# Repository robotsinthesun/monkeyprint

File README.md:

# monkeyprint
A simple tool for pre-processing 3d models and controlling 3d DLP printers.

## What is *monkeyprint* for?
*monkeyprint* came into existence as an open source, will-natively-run-on-linux alternative to [*Creation Workshop*](http://www.envisionlabs.net/home.html).

Thanks to the latest efforts it also runs on Windows although it has not been thoroughly tested yet...

####*monkeyprint* allows you to:

* load one or multiple stl files
* define the position, scale or rotation in the printers build volume
* generate supports with some simple parameters
* hollow the model and create fill structures
* slice the model with a specific layer height
* control a print job on your DLP printer via serial port using G-Code commands

In order for *monkeyprint* to work you need a 3d DLP printer that can receive G-Code commands via serial port and has a projector that is connected to your PC.

## Installation

#### Dependencies
*monkeyprint* is programmed in Python 2.7 and uses the following libraries:

* `PyQt4` for the GUI
* `VTK` for stl processing and slicing
* `openCV` for slice image handling
* `numpy` for slice image handling
* `pyserial` and `zmq` for communication

#### Linux installation

\* **Using a virtualenv**

Create a virtual env with python2.7 as the interpreter and activate it.

For installing PyQt4, execute the following commands (assigning your virtualenv 
path to the $virtual_env_path variable)

```bash
$  sudo apt-get install python-qt4

$  $virtual_env_path="your/virtualenv/path"
$  cp -R  /usr/lib/python2.7/dist-packages/sip* $virtual_env_path/lib/python2.7/site-packages
$  mkdir $virtual_env_path/lib/python2.7/site-packages/PyQt4/
$  cp -R  /usr/lib/python2.7/dist-packages/PyQt4/* $virtual_env_path/lib/python2.7/site-packages/PyQt4/

```

```bash
$  pip install -r /monkeyprint_repo_path/requirements.txt
```

\* **Installing globally**

First, install the dependencies.
On Debian-based distros like Ubuntu, you can install the relevant packages using the following command:

`sudo apt-get install git-core python-qt4 libvtk5.8 libopencv-core2.4 python2.7 python-vtk python-numpy python-opencv python-imaging python-serial python-zmq`

Once the dependencies are installed, simply download *monkeyprint* using git:

`git clone git://github.com/robotsinthesun/monkeyprint.git`

This will create a monkeyprint folder in your current location. You can then start *monkeyprint* by running `python monkeyprint.py` from within that folder.

#### Windows installation

Windows users simply download the latest release [here](https://github.com/robotsinthesun/monkeyprint/releases). It's an exe that contains Python and all the necessary libraries. No need to install anything. Yep.

#### Hardware
*monkeyprint* controls your printer using G-Code, so if your printer connects via serial or usb and understands G-Code, you're good to go. Alternatively, you can define custom string commands if your board uses some other language.

## Basic setup

Before starting to use *monkeyprint* with your printer, it is necessary to adjust some of the settings to fit your machine.

Start *monkeyprint*, click *Options* in the top menu and select *Settings*. A dialog will come up.

#### Main settings
In the first tab, make sure to correctly set

* your printers build volume (the size of the area illuminated by your projector and the draw of your Z-axis),
* the serial connection to your printer's controller board. On Linux, this will most likely be `/dev/ttyACM0` or `/dev/ttyUSB0` if you're connecting via USB or `/dev/ttyS0` if using an old-school Sub-D serial connection while on Windows it will be something like `COM0` or `COM1`. The baud rate depends on the board you use and should be in the manual. On most boards it will be `57600` or `115200`.

Adjust the *Max. preview slices* if you wish. In the slicer preview, you will be presented an evently spaced number of preview slices as a subsample of all the slices. The default of 300 should be enough as the slider does not allow for finer control anyways.

Tick the *Multi body slicing* option if your model contains intersecting objects within the same stl file.

#### Projector settings
In the second tab the projector settings will be set up. These are

* your projectors resolution in pixels. This should be self-explaining...
* your projectors "position", i.e. the location of it's top left corner in relation to the whole desktop. For *monkeyprint* to work, your projector should be connected via *HDMI* and should be set to *extend* the desktop. So, if you move your mouse beyond one of the sides of your main screen, it should appear on the projector. If the projector is to the right of your main screen and the latter has a resolution of 1024 x 768 pixels, your projectors position will most likely be `1024, 0`
* an optional serial connection to your projector. Some projectors support the old Sub-D serial connector. If you get yourself a USB-to-serial adapter you will be able to connect that to your PC and power your projector on and off automatically before and after prints. The usual parameters for this connection are set as defaults, simply adjust the serial port setting to the one of your USB-to-serial adapter and it should work.

#### Print process settings
Here, you are able to construct your print process from individual modules. There are two basic types of module: internal modules and G-Code modules. While the internal modules run a distinct function like doing the exposure or simply waiting for a user-defined interval, G-Code modules send a command to your printer via serial connection.

There are three sections during a print process:

* The start section can be used to do all the tasks that bring your printer into its ready-to-print state e.g. powering up the projector, homing the build platform etc.
* The print loop section runs the commands necessary to print a slice, e.g. exposing, moving the build platform, tilting etc. for each of the slices.
* The stop section can be used to do stuff after the print has finished, e.g. moving the build platform into top position, shutting down the projector etc.

The controls below the print process list allow for adding new modules, moving the selected module up or down and deleting a selected module (except for the *Start loop* and *End loop* modules).

* To add a new module, select one from the dropdown and click the *Add* button. The new module will be inserted below the currently selected one.
* The other buttons are pretty much self-explaining I guess...
* To change the name or value of a module, simply double click the name or value in the list and enter a new one. Note: there is no checking for valid G-Code commands, so make sure they make sense and are accepted by your printer.

Here is a list of the available modules:

* *Expose*: exposes the VAT for the exposure time set in the main gui.
* *Wait*: waits for the given interval
* *Projector on / off*: Starts / shuts down your projector using the commands and serial connection specified in the *Projector settings*
* *Start / end loop*: use this to separate start, print loop and stop section
* *Custom G-Code*: sends the given command string to your printer via the serial connection specified in the main settings

## Usage

The *monkeyprint* gui is made to walk you through the pre-processing steps up to starting the print.
The model and it's position is shown in the 3d view on the left while the tabs on the right will guide you through the necessary settings.

First, load a model file by clicking the "Load model" button. Set it's scaling, position and rotation.
The model will automatically fitted to the build volume if the scaling is too large.

Proceed to the "Slicing" tab. Here you can set the overhang angle and define the geometry of the support pillars. You can also define the thickness of the bottom plate.
You can also play with the "Maximum support height" option to eliminate unwanted supports.

In the "Slicing" tab you can set the layer height and walk through the model by using the slider.
The "Print hollow" and "Use fill structures" should be self explaining. Printing hollow reduces the force on the coating of the VAT and helps to elongate the coatings life.

The "Print" tab finally let's you start the print.
Set the exposure values and hit "Print!". Complete the safety check list and there you go: your print is running!
Cancel the print by pressing "Stop". It won't stop immediately but complete the current slice and run the Stop sequence commands.

Note that you can't close the program while a print is running.

## Testing an debugging

You can simulate a serial port in order to debug the program locally:

```bash
$  socat -d -d pty,raw,echo=0 pty,raw,echo=0
```

You will receive an output like this

```bash
2019/07/30 13:01:23 socat[14810] N PTY is /dev/pts/4
2019/07/30 13:01:23 socat[14810] N PTY is /dev/pts/5
2019/07/30 13:01:23 socat[14810] N starting data transfer loop with FDs [5,5] and [7,7]
```

Now, in a new terminal execute:

```bash
$  cat < /dev/pts/4
```

*Note: The number can be different for you

Finally, inside the program settings, choose */dev/pts/5* as the serial port. Then,
start the printing.

The G-codes sent via serial port can now be monitored in the terminal.

The program will retry a command if there is no printer response. 
You can simulate the printer response by doing:

```bash
$  echo "ok" > /dev/pts/4
```

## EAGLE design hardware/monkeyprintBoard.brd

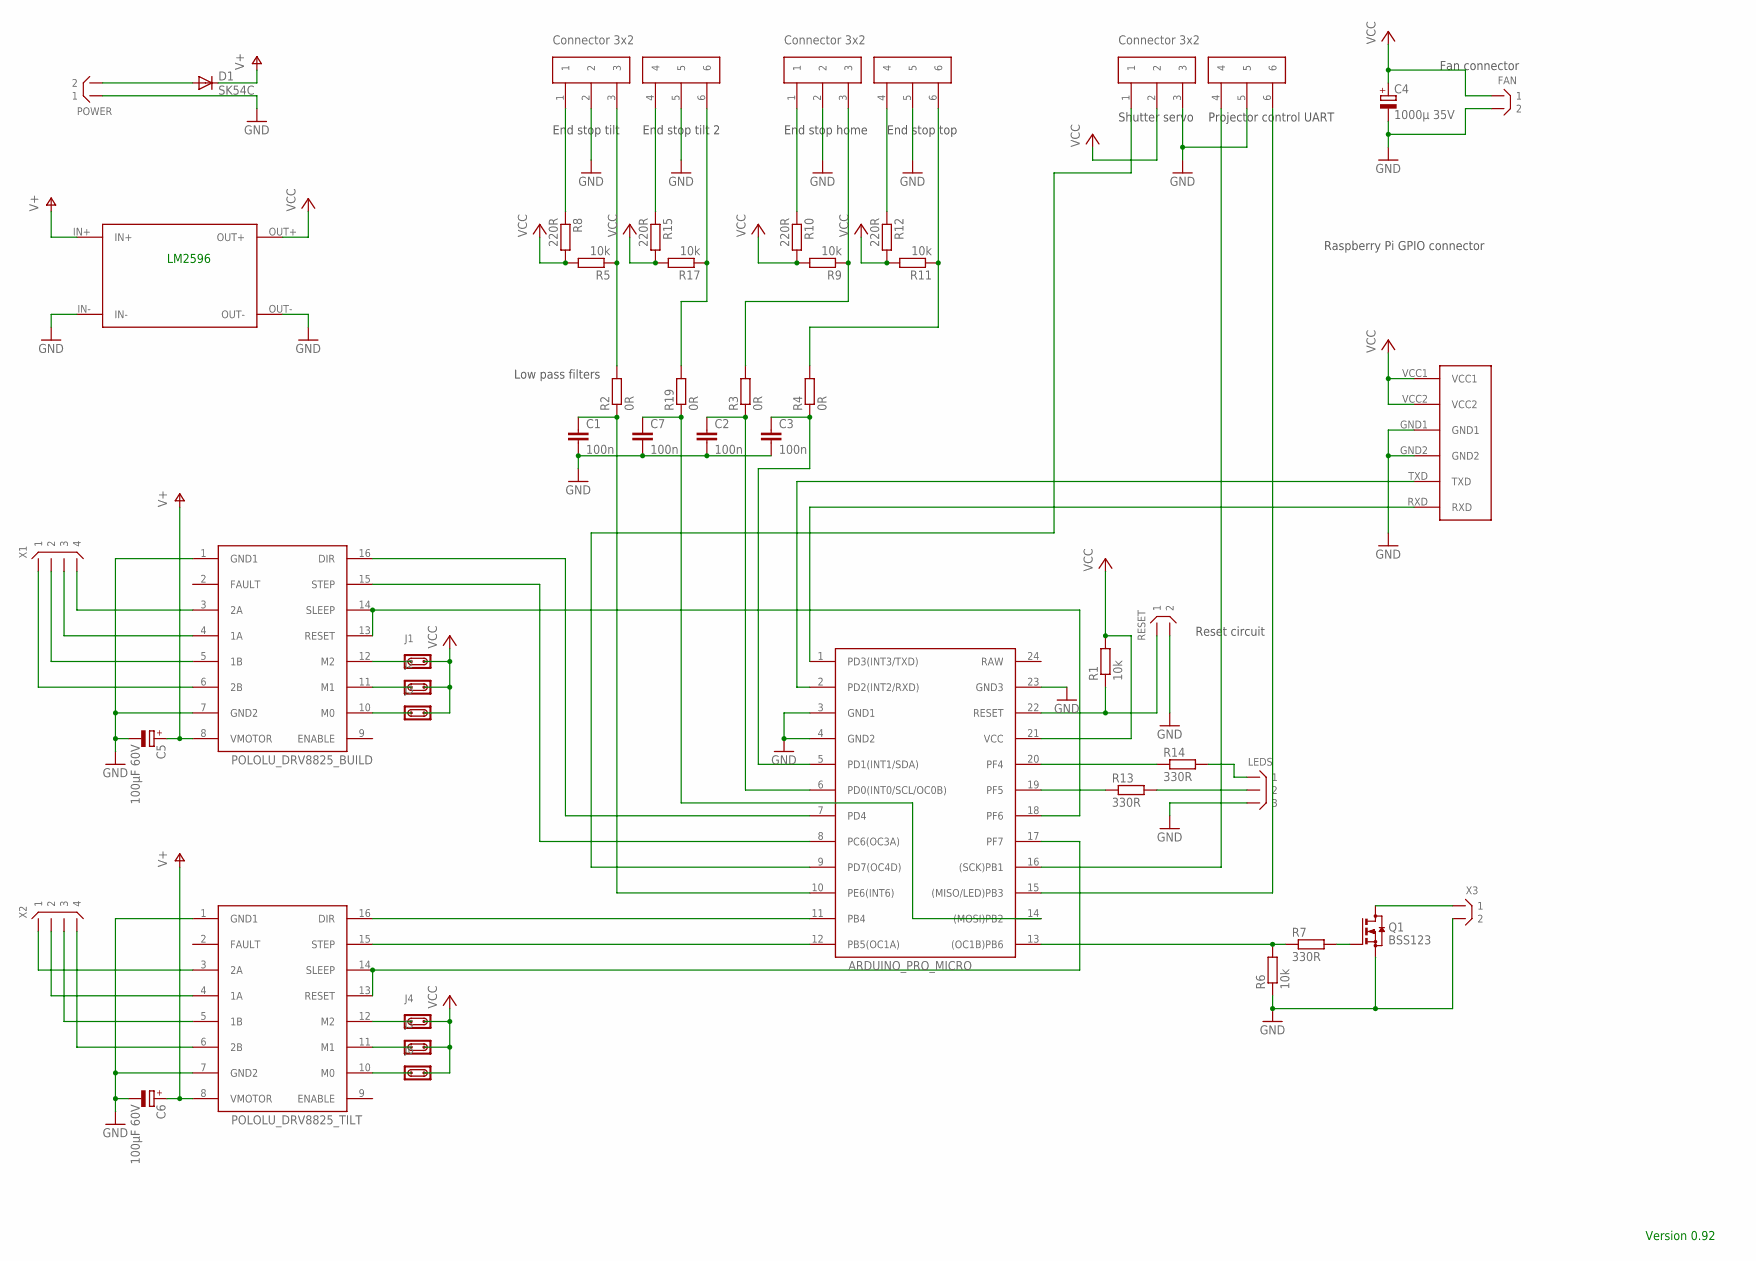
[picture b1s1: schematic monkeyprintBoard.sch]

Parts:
ARDUINO_PRO_MICRO: ARDUINOPROMICRO
C1, C2, C3, C7: 100n; C0603
C4: 1000µ 35V; E5-10,5
C5, C6: 100µF 60V; E5-10,5
D1: SK54C; SMC
FAN: X02; X02N-SIL
J1, J2, J3, J4, J5, J6: JP02; JP02N
LEDS: X03; X03N-SIL
POLOLU_DRV8825_BUILD, POLOLU_DRV8825_TILT: POLOLU8825
POWER: X02; X02N-SIL
Q1: BSS123; SOT23
R1, R5, R6, R9, R11, R17: 10k; R0603
R2, R3, R4, R19: 0R; R0603
R7, R13, R14: 330R; R0603
R8, R10, R12, R15: 220R; R0603
RESET: X02; X02N-SIL
U$1: MONKEYPRINTPICONNECTOR
U$4: LM2596MODULEUPRIGHT
U$5, U$6, U$7: CON3X2; CONNECTOR3X2
X1, X2: X04; X04N-SIL
X3: X02; X02N-SIL

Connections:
GND: ARDUINO_PRO_MICRO.3 (GND1), ARDUINO_PRO_MICRO.4 (GND2), ARDUINO_PRO_MICRO.23 (GND3), C1.2, C2.2, C3.2, C4.-, C5.-, C6.-, C7.2, FAN.2, LEDS.3, POLOLU_DRV8825_BUILD.1 (GND1), POLOLU_DRV8825_BUILD.7 (GND2), POLOLU_DRV8825_TILT.1 (GND1), POLOLU_DRV8825_TILT.7 (GND2), POWER.1, Q1.2 (S), R6.1, RESET.2, U$1.GND1, U$1.GND2, U$4.IN-, U$4.OUT-, U$5.2, U$5.5, U$6.2, U$6.5, U$7.3, U$7.5, X3.2
unnamed: ARDUINO_PRO_MICRO.7 (PD4), POLOLU_DRV8825_BUILD.16 (DIR)
unnamed: ARDUINO_PRO_MICRO.8 (PC6(OC3A)), POLOLU_DRV8825_BUILD.15 (STEP)
unnamed: R2.2, R5.1, U$6.3
unnamed: ARDUINO_PRO_MICRO.12 (PB5(OC1A)), POLOLU_DRV8825_TILT.15 (STEP)
unnamed: ARDUINO_PRO_MICRO.18 (PF6), POLOLU_DRV8825_BUILD.13 (RESET), POLOLU_DRV8825_BUILD.14 (SLEEP)
unnamed: ARDUINO_PRO_MICRO.11 (PB4), POLOLU_DRV8825_TILT.16 (DIR)
unnamed: R3.2, R9.1, U$5.3
unnamed: ARDUINO_PRO_MICRO.17 (PF7), POLOLU_DRV8825_TILT.13 (RESET), POLOLU_DRV8825_TILT.14 (SLEEP)
unnamed: R4.2, R11.1, U$5.6
unnamed: R8.1, U$6.1
unnamed: R10.1, U$5.1
unnamed: ARDUINO_PRO_MICRO.5 (PD1(INT1/SDA)), C3.1, R4.1
unnamed: ARDUINO_PRO_MICRO.6 (PD0(INT0/SCL/OC0B)), C2.1, R3.1
unnamed: R12.1, U$5.4
unnamed: POLOLU_DRV8825_BUILD.3 (2A), X1.4
unnamed: POLOLU_DRV8825_BUILD.4 (1A), X1.3
unnamed: POLOLU_DRV8825_BUILD.5 (1B), X1.2
unnamed: POLOLU_DRV8825_TILT.3 (2A), X2.1
unnamed: POLOLU_DRV8825_TILT.4 (1A), X2.2
unnamed: POLOLU_DRV8825_TILT.5 (1B), X2.3
unnamed: POLOLU_DRV8825_TILT.6 (2B), X2.4
unnamed: J6.1, POLOLU_DRV8825_TILT.10 (M0)
unnamed: J5.1, POLOLU_DRV8825_TILT.11 (M1)
unnamed: J4.1, POLOLU_DRV8825_TILT.12 (M2)
unnamed: ARDUINO_PRO_MICRO.10 (PE6(INT6)), C1.1, R2.1
unnamed: ARDUINO_PRO_MICRO.1 (PD3(INT3/TXD)), U$1.RXD
unnamed: ARDUINO_PRO_MICRO.13 ((OC1B)PB6), R6.2, R7.1
unnamed: ARDUINO_PRO_MICRO.22 (RESET), R1.1, RESET.1
unnamed: ARDUINO_PRO_MICRO.16 ((SCK)PB1), U$7.4
unnamed: Q1.1 (G), R7.2
unnamed: Q1.3 (D), X3.1
unnamed: ARDUINO_PRO_MICRO.19 (PF5), R13.1
unnamed: ARDUINO_PRO_MICRO.21 (VCC), R1.2
unnamed: ARDUINO_PRO_MICRO.20 (PF4), R14.1
unnamed: LEDS.2, R13.2
unnamed: LEDS.1, R14.2
unnamed: ARDUINO_PRO_MICRO.2 (PD2(INT2/RXD)), U$1.TXD
unnamed: ARDUINO_PRO_MICRO.15 ((MISO/LED)PB3), U$7.6
unnamed: ARDUINO_PRO_MICRO.9 (PD7(OC4D)), U$7.1
unnamed: D1.A, POWER.2
unnamed: R15.1, U$6.4
unnamed: POLOLU_DRV8825_BUILD.6 (2B), X1.1
unnamed: C5.+, POLOLU_DRV8825_BUILD.8 (VMOTOR)
unnamed: J3.1, POLOLU_DRV8825_BUILD.10 (M0)
unnamed: J2.1, POLOLU_DRV8825_BUILD.11 (M1)
unnamed: J1.1, POLOLU_DRV8825_BUILD.12 (M2)
unnamed: R17.1, R19.2, U$6.6
unnamed: ARDUINO_PRO_MICRO.14 ((MOSI)PB2), C7.1, R19.1
V+: C6.+, D1.C, POLOLU_DRV8825_TILT.8 (VMOTOR), U$4.IN+
VCC: C4.+, FAN.1, J1.2, J2.2, J3.2, J4.2, J5.2, J6.2, R5.2, R8.2, R9.2, R10.2, R11.2, R12.2, R15.2, R17.2, U$1.VCC1, U$1.VCC2, U$4.OUT+, U$7.2

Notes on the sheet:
Fan connector
End stop tilt 2
Projector control UART
End stop top
End stop home
End stop tilt
Low pass filters
Shutter servo
Reset circuit
LM2596
Raspberry Pi GPIO connector
Version 0.92

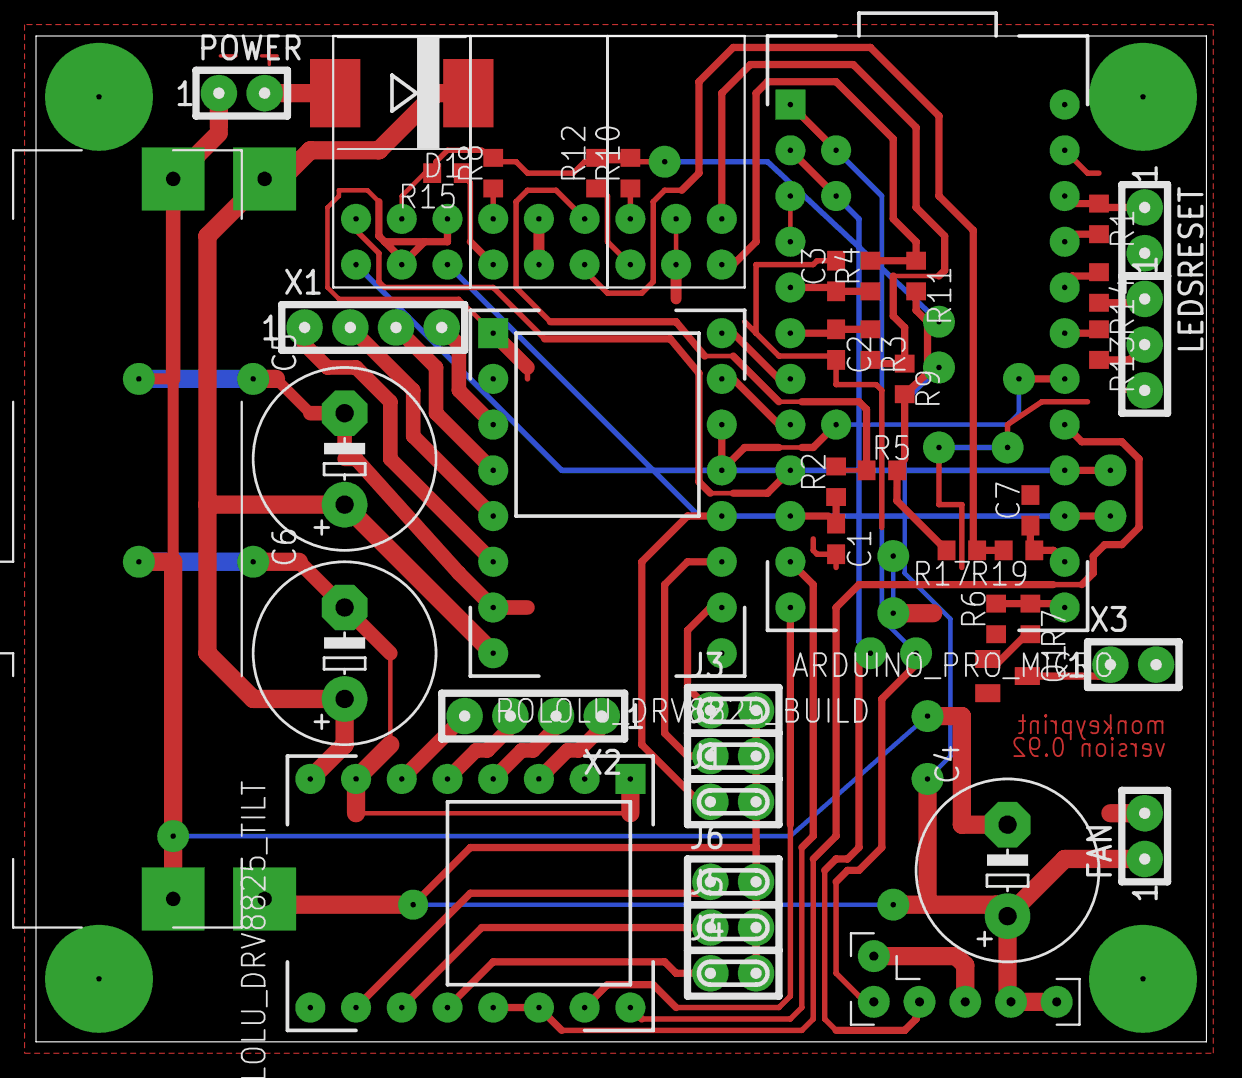
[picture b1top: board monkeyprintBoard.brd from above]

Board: 2 copper layers, 65.0 x 55.9 mm, 47 parts (0 on the bottom side), 51 nets.

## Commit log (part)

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2015-08-09 First alpha upload. Working but improvable
2015-08-09 Updated readme file
2015-10-26 Started redesign with GTK and including firmware for AtMega32U4.
2015-10-27 Implemented enable/disable behaviour for settings tabs, fixed current folder for model file loader, added supports to VTK pipeline.
2015-10-29 Implemented custom class for gtk.Notebook to handle tab change events, completed support generation methods.
2015-11-01 Started model slicing reimplementation + finished supports generation stuff.
2015-11-04 Started slice stack implementation for multiple object print. Added slice preview class
2015-11-05 Fixed gui tab behaviour
2015-11-08 Implemented new method to update 3d view with moving slice.
2015-11-10 Implemented slice image generation function to generate slice images indepent of the slice preview in the GUI
2015-11-10 Fixed slice preview update function
2015-11-12 Updated slicer background thread, implemented input and output queues
2015-11-15 Fixed slice image stencil position from px to mm
2015-11-15 Fixed interaction between GUI and slicer threads, implemented clean-up on shutdown, cleaned up model data class.
2015-11-17 Implemented print progress status bar
2015-11-19 Implemented Start and Stop Print dialog boxes.
2015-11-25 Added projector display window class
2015-11-27 Implemented methods for settings to be read from and written to a file.
2015-11-27 Merged GUI classes, cleaned up GUI code. Fixed model load dialog cancel behaviour.
2015-11-27 Fixed defaults for avrdude settings.
2015-11-29 Implemented avrdude thread to prevent gui blocking
2015-11-29 Implemented manual control dialog and connected the serial port thread.
2015-11-30 Set up communication between serial process and gui.
2015-12-02 Fixed debug model checkbox in settings menu.
2015-12-03 Implemented projector control entries in settings menu. Connected Quit item in menu to close function.
2015-12-03 Added documentation menu items.
2015-12-04 Fixed print process communication.
2015-12-04 Fixed gui behaviour after finished print job
2015-12-06 Added model collection file save and load methods.
2015-12-06 "Moved menu bar creation to main gui class."
2015-12-06 Fixed menu item sensitivity behaviour.
2015-12-07 Fixed model selection upon project loading, implemented close function, fixed model list view behaviour in gui.
2015-12-07 Added confirm dialog to Close Project menu item.
2015-12-07 Added layer height and stepper configuration commands to print process and firmware.
2015-12-08 Added tilt stepper control methods to print process and firmware.
2015-12-08 Made settings-, firmware- and manual controll dialogs modal and transient.
2015-12-08 Implemented tilt stepper ramping.
2015-12-08 Implemented automatic stepper switch off when not printing.
2015-12-08 Fixed homing interrupt issue.
2015-12-09 Implemented camera trigger on pin B6.
2015-12-10 Fixed gui sensitivity and model visibility on model actvie state change.
2015-12-10 Fixed camera trigger debug mode behaviour.
2015-12-10 Fixed uncontrolled slicer restarts.
2015-12-11 Added print process file which should have been added days ago...
2015-12-11 Fixed build platform homing ramp down error on start up.
2015-12-12 Fixed string to bool conversion during settings file loading.
2015-12-14 Implemented ghost model for deactivated models, fixed slice tab entry sensitivity for deactivated models.
2015-12-24 Firmware: Added UART serial communication for use with Raspberry Pi. Moved USB virtual serial receive function to virtual serial lib.
2015-12-25 Firmware: Added UART receive function to command string evaluation. Firmware now receives commands from USB virtual serial and from UART.
2015-12-25 Firmware: Added files for uart and command evaluation which I forgot in the previous two commits.
2015-12-25 Fixed include file for itoa() and atoi().
2015-12-25 Firmware: Some clean-ups.
2015-12-29 Added numpy dilate and erode image functions in order to replace opencv.
2016-01-01 Implemented option to enable or disable tilt for top down printer designs .
2016-01-01 Removed matplotlib dependency
2016-01-01 Added eagle hardware schematics as pdf.
2016-01-01 Added eagle hardware schematics as image.
2016-02-17 Changed settings dialog to notebook style, added calibration image.
2016-02-22 Updated eagle files.
2016-02-24 Added compoentent placement guide, minor changes to board.
2016-03-11 Implemented non gui standalone print process to run on rapsberry pi.
2016-03-15 Added shutter servo routines to firmware.
2016-03-15 Added missing VCC line in component placement guide.
2016-03-24 Added main.hex so you do not need to compile the firmware...
2016-03-24 Fixed typo in model collection.
2016-04-16 Changed project saving code to include stl files in Monkeyprint project (mkp) files. This is necessary to send project files to the Raspberry Pi.
2016-04-16 Changed project load code to read mkp file that includes the stl files. This is necessary for using Monkeyprint on the Raspberry Pi.
2016-04-17 Added debug command line option. Debug mode will run without serial connection to the Monkeyprint board.
2016-05-09 Added splash screen on startup.
2016-05-16 Changes to splash screen and project load function.
2016-05-16 Added example project file.
2016-05-17 Added Raspberry Pi options to settings dialog.
2016-05-23 Added projector control command settings to settings dialog.
2016-06-04 Added Monkeyprint server that runs on Raspberry Pi
2016-06-04 Added socket communication code using zmq.
2016-06-04 Fixed Raspberry Pi slice image position.
2016-06-04 Fixed socket settings.
2016-06-20 Completed raspberry pi communication prototype via sockets.
2016-06-21 Fixed communication time lag between print process thread and gui. Exposure times are rock solid now...
2016-06-21 Fixed typo.
2016-06-21 Fixed file clean up for server after print.
2016-06-22 Added port selection for Raspberry Pi to serial port class.
2016-06-26 Fixed firmware serial ack issues.
2016-06-26 Changed packet delay for file transmission.
2016-06-26 Fixed settings file location in Raspberry server mode.
2016-06-26 Added print process exit if serial connection broken.
2016-06-26 Added serial debug messages.
2016-06-26 Changed build platform to move before exposure, not after.
2016-06-26 Fixed wait time before print start on Raspberry.
2016-06-29 Rewrite of print thread to GUI communication methods.
2016-07-03 Preparations for merging standalone GUI and server classes.
2016-07-03 Small fixes.
2016-07-03 Fixes...
2016-07-03 Fixes #4: Changed model handling methods to work with VTK 6 API.
2016-07-03 Fixed slice display in GUI during prints from Raspberry.
2016-07-03 Added install script for Raspberry Pi
2016-07-04 Small fix to raspberry pi install script.
2016-07-04 Another small fix to raspberry pi install script.
2016-07-05 Added experimental G-Code support.
2016-07-06 Firmware reupload.
2016-07-08 Disabled obscure settings for build stepper.
2016-07-12 Small fixes to communication queue.
2016-09-05 Fix for line breaks in settings file.
2016-09-25 New example project file and minor fixes.
2016-10-02 Fix for typo in settings object.
2016-10-18 Set lower bound for model scaling to avoid div by 0 error.
2016-10-18 Make MP compatible with python-pillow library
    The PIL library is deprecated/abandonned and Pillow is the new fork
    which is compatible with PIL, however, it requires the imports to be
    done using the 'from PIL import X' instead of 'import X', so this change
    will allow MP to use either PIL or Pillow, regardless of what is
    available on the system.
2016-10-19 Partial fix for slicer that prevents crashes. Slicer runs without crash but gui freezes afterwards sometimes.
2016-10-25 VTK6: Fix slicing by using SetStencilConnection instead of SetStencilData
    This should fix https://github.com/robotsinthesun/monkeyprint/issues/4
2016-10-26 Reactivated hollowing and fill features for slicer.
2016-10-26 Set version string.
2016-10-27 Added isConstant flag to settings that my not be changed by program.
2016-10-27 Changed revision number.
2016-10-29 Implemented new slice polyline to image algorithm for a significant slicer speed increase. This get's rid of some VTK dependent code in favour of numpy based code.
2016-11-02 Improved slicer algorithm that tries to automatically close open cut polyines on corrupt meshes.
2016-11-04 Remove trailing whitespaces from the file
    This commit doesn't change anything but the trailing whitespaces. My emacs
    config has 'show-trailing-whitespaces' enabled so all whitespaces appear
    red in the file, which is very annoying. I've cleaned up the whitespaces
    using the 'whitespace-cleanup' command of emacs.
2016-11-05 Fixed holes in model outer wall due to hollowing. Major improvements to hollowing and slice generation methods that provide another slight speed-up.
2016-11-05 Including VTK6 proposed by Kakaroto.
2016-11-11 Implemented slice combiner that reads the model slice images from the respective files and produces a preview slice stack with predefined number of slices.
2016-11-17 Rewrite of slice stack export function with new slice combiner.
2016-11-17 Rename confusing set and get methods for jobSettings.
2016-11-27 Changed model update functions to run if specific settings have been changed. Fixed gui workflow on settings change (model, supports, slicer and print tab sensitivities). Reimplemented calibration im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
2016-12-06 Redesign of slicer thread communication to avoid non-thread-safe access to programSettings, implementation of safety border in slice images to avoid errors during erosion if slices touch slice image 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
2016-12-06 Added error catcher for vtk warnings.
2016-12-06 Rearranged erosion (hollowing) code for slight speed up, cleaned up slicer code.
2016-12-06 Updated version number
2016-12-18 Added option in settings dialog to enable or disable the multi body slicer.
2016-12-19 Code clean-up
2016-12-20 Implemented multiple base layers with separate exposure values.
2016-12-20 Increase version number to 0.13.0
    #19 fixed
    #20 fixed
2017-11-04 Started implementing slice slider
2017-12-05 Implemented functionality of model, support and slicing tab.
2018-01-13 Finished basic GUI implementation. Print process is running again.
2018-01-13 Implemented settings window except for print process model view.
2018-01-14 Added splash screen.
2018-01-26 Implement dummy table model for print process table view.
2018-01-31 Finish main work on translation from GTK to PyQt
2018-01-31 Remove GTK references
2018-01-31 Fix wrong slice preview labels in slider
2018-01-31 Fix splash screen, increment version string to 0.13.0
2018-01-31 Fix slice save progress dialog.
2018-01-31 Fix mismatching number of slices in slice image save method.
2018-01-31 Fix (again) thread join issue upon closing on Windows
2018-02-01 Improve readme file. Prevent Start loop and End loop commands from being removed.
2018-02-02 Modified readme for Windows install, added Windows packaging notes
2018-02-02 Move install path detection to settings
2018-02-02 Add packaging spec file for pyinstaller
2018-02-05 Start mesh class implementation
2018-02-10 Fix version string overwrite behaviour, add x86 build instructions
2018-03-30 Start mesh kernel implementation
2018-03-31 Add normals recalculation to stl loader
2018-03-31 Add mesh connectivity computation to stl loader
2018-03-31 Add scale method
2018-03-31 Add QWidget OpenGL render view
2018-04-05 Add simple object database and color picking to OpenGL test
2019-07-30 Add Minor fixes & extend docs
    Adjust code for compatibility with OpenCV4.
    Add requirements file and documentation for setting up the app
    using virtualenv
2019-07-31 HotFix: Do not turn on the projector when starting the loop
2019-08-01 Fix diverse bugs
    Set a Black display screen when the printing is finished
    Erase the upper boundary for exposition time
    Load the settings properly
2019-08-02 Print the estimated time in console
    This is a first version. Further testing is needed
